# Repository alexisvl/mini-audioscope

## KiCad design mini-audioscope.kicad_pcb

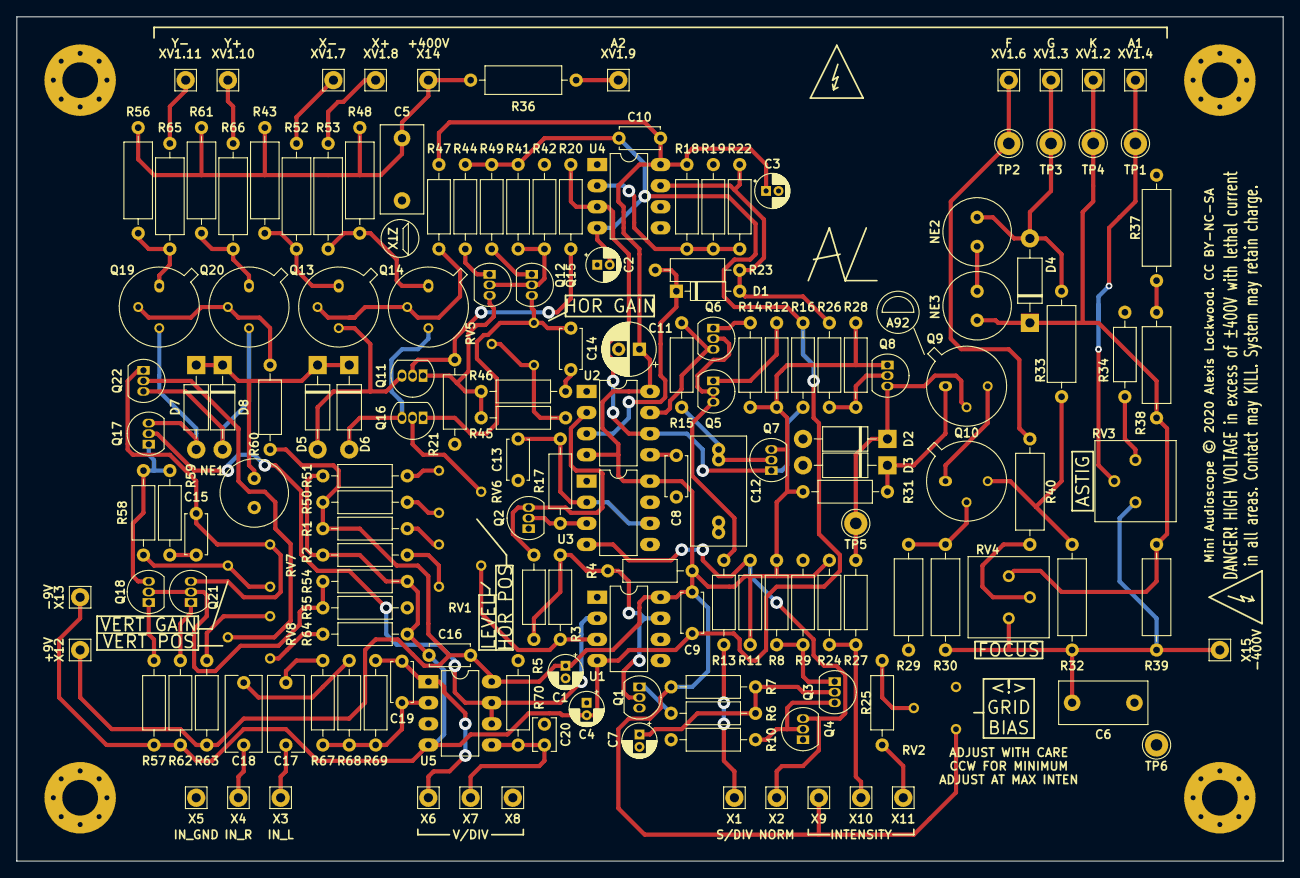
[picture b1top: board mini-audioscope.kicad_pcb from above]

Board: 2 copper layers, 152.4 x 101.6 mm, 169 parts (0 on the bottom side), 90 nets.

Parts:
C1, C2, C3, C4: 33µ; CP_Radial_D4.0mm_P1.50mm
C5, C6: 22n; C_Disc_D10.5mm_W5.0mm_P7.50mm
C7: 3µ3; CP_Radial_D4.0mm_P1.50mm
C8: 10n; C_Disc_D4.7mm_W2.5mm_P5.00mm
C9, C10, C16: 100n; C_Disc_D4.7mm_W2.5mm_P5.00mm
C11: 47µ; CP_Radial_D6.3mm_P2.50mm
C12: 470n; C_Rect_L13.0mm_W6.5mm_P7.50mm_P10.00mm
C13: 470n; C_Disc_D4.7mm_W2.5mm_P5.00mm
C14, C15: DNP; C_Disc_D4.7mm_W2.5mm_P5.00mm
C17, C18: 220n; C_Rect_L9.0mm_W4.2mm_P7.50mm_MKT
C19: 47p; C_Disc_D4.7mm_W2.5mm_P5.00mm
C20: 22p; C_Disc_D3.8mm_W2.6mm_P2.50mm
D1: 1N4148; D_DO-35_SOD27_P7.62mm_Horizontal
D2, D3, D4, D5, D6, D7, D8: 1N4007; D_DO-41_SOD81_P10.16mm_Horizontal
H1, H2, H3, H4: GND; MountingHole_4.3mm_M4_Pad_Via
NE1, NE2, NE3: A9A; C_Radial_D8.0mm_H11.5mm_P3.50mm
Q1, Q3, Q5, Q6, Q8: 2N3906; TO-92_Inline
Q2: 2N7000; TO-92_Inline
Q4, Q7, Q12, Q15, Q18, Q21: 2N3904; TO-92_Inline
Q9, Q10: MPSA92; TO-5-3
Q11, Q16, Q17, Q22: 2N5551; TO-92_Inline
Q13, Q14, Q19, Q20: ZTX458; TO-5-3
R1, R2: 27k; R_Axial_DIN0207_L6.3mm_D2.5mm_P10.16mm_Horizontal
R3, R22: 4M7; R_Axial_DIN0207_L6.3mm_D2.5mm_P10.16mm_Horizontal
R4, R8, R11, R18, R19, R20, R23, R27, R41, R42, R47, R54, R55, R60: 10k; R_Axial_DIN0207_L6.3mm_D2.5mm_P10.16mm_Horizontal
R5, R7, R10, R67, R68, R69: 100k; R_Axial_DIN0207_L6.3mm_D2.5mm_P10.16mm_Horizontal
R6: 10; R_Axial_DIN0207_L6.3mm_D2.5mm_P10.16mm_Horizontal
R9: 22k; R_Axial_DIN0207_L6.3mm_D2.5mm_P10.16mm_Horizontal
R12, R13, R14: 470; R_Axial_DIN0207_L6.3mm_D2.5mm_P10.16mm_Horizontal
R15: 100; R_Axial_DIN0207_L6.3mm_D2.5mm_P10.16mm_Horizontal
R16: 6k8; R_Axial_DIN0207_L6.3mm_D2.5mm_P10.16mm_Horizontal
R17: 75k; R_Axial_DIN0207_L6.3mm_D2.5mm_P10.16mm_Horizontal
R21: 2k7; R_Axial_DIN0207_L6.3mm_D2.5mm_P10.16mm_Horizontal
R24: 470k; R_Axial_DIN0207_L6.3mm_D2.5mm_P10.16mm_Horizontal
R25: 1k; R_Axial_DIN0207_L6.3mm_D2.5mm_P10.16mm_Horizontal
R26: 33k; R_Axial_DIN0207_L6.3mm_D2.5mm_P10.16mm_Horizontal
R28, R34: 180k; R_Axial_DIN0207_L6.3mm_D2.5mm_P10.16mm_Horizontal
R29, R30, R32, R39, R43, R48, R56, R61: 220k/HW; R_Axial_DIN0309_L9.0mm_D3.2mm_P12.70mm_Horizontal
R31: 20k; R_Axial_DIN0207_L6.3mm_D2.5mm_P10.16mm_Horizontal
R33, R40: 100k/HW; R_Axial_DIN0309_L9.0mm_D3.2mm_P12.70mm_Horizontal
R36, R52, R53, R65, R66: 10k/HW; R_Axial_DIN0309_L9.0mm_D3.2mm_P12.70mm_Horizontal
R37, R38: 390k/HW; R_Axial_DIN0309_L9.0mm_D3.2mm_P12.70mm_Horizontal
R44, R49, R50, R51, R57, R62, R63, R64: 8k2; R_Axial_DIN0207_L6.3mm_D2.5mm_P10.16mm_Horizontal
R45, R58: 1k5; R_Axial_DIN0207_L6.3mm_D2.5mm_P10.16mm_Horizontal
R46, R59: DNP; R_Axial_DIN0207_L6.3mm_D2.5mm_P10.16mm_Horizontal
R70: 1M; R_Axial_DIN0207_L6.3mm_D2.5mm_P10.16mm_Horizontal
RV1, RV2, RV5, RV7: 5k; stock_pot
RV3: 500k; Potentiometer_Bourns_3386P_Vertical
RV4: 1M; Potentiometer_Bourns_3386P_Vertical
RV6, RV8: 2k; stock_pot
TP1: V(A1); TestPoint_Loop_D2.60mm_Drill1.4mm_Beaded
TP2: V(F); TestPoint_Loop_D2.60mm_Drill1.4mm_Beaded
TP3: V(G); TestPoint_Loop_D2.60mm_Drill1.4mm_Beaded
TP4: V(K); TestPoint_Loop_D2.60mm_Drill1.4mm_Beaded
TP5: INTEN; TestPoint_Loop_D2.60mm_Drill1.4mm_Beaded
TP6: GND; TestPoint_Loop_D2.60mm_Drill1.4mm_Beaded
U1, U4: LM311; DIP-8_W7.62mm_LongPads
U2, U3: NE555P; DIP-8_W7.62mm_LongPads
U5: TL072; DIP-8_W7.62mm_LongPads
X1: S/DIV; Pin_D1.1mm_L8.5mm_W2.5mm_FlatFork
X2: NORM; Pin_D1.1mm_L8.5mm_W2.5mm_FlatFork
X3: L; Pin_D1.1mm_L8.5mm_W2.5mm_FlatFork
X4: R; Pin_D1.1mm_L8.5mm_W2.5mm_FlatFork
X5: G; Pin_D1.1mm_L8.5mm_W2.5mm_FlatFork
X6: G+; Pin_D1.1mm_L8.5mm_W2.5mm_FlatFork
X7: GW; Pin_D1.1mm_L8.5mm_W2.5mm_FlatFork
X8: G-; Pin_D1.1mm_L8.5mm_W2.5mm_FlatFork
X9: I+; Pin_D1.1mm_L8.5mm_W2.5mm_FlatFork
X10: IW; Pin_D1.1mm_L8.5mm_W2.5mm_FlatFork
X11: I-; Pin_D1.1mm_L8.5mm_W2.5mm_FlatFork
X12: +9; Pin_D1.1mm_L8.5mm_W2.5mm_FlatFork
X13: -9; Pin_D1.1mm_L8.5mm_W2.5mm_FlatFork
X14: +400; Pin_D1.1mm_L8.5mm_W2.5mm_FlatFork
X15: -400; Pin_D1.1mm_L8.5mm_W2.5mm_FlatFork
XV1.2: K; Pin_D1.1mm_L8.5mm_W2.5mm_FlatFork
XV1.3: G; Pin_D1.1mm_L8.5mm_W2.5mm_FlatFork
XV1.4: A1; Pin_D1.1mm_L8.5mm_W2.5mm_FlatFork
XV1.6: F; Pin_D1.1mm_L8.5mm_W2.5mm_FlatFork
XV1.7: X-; Pin_D1.1mm_L8.5mm_W2.5mm_FlatFork
XV1.8: X+; Pin_D1.1mm_L8.5mm_W2.5mm_FlatFork
XV1.9: A2; Pin_D1.1mm_L8.5mm_W2.5mm_FlatFork
XV1.10: V+; Pin_D1.1mm_L8.5mm_W2.5mm_FlatFork
XV1.11: V-; Pin_D1.1mm_L8.5mm_W2.5mm_FlatFork

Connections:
+9V: C1.1, C3.1, C9.1, C10.1, C11.1, C16.2, Q7.3, Q8.1, R1.2, R4.1, R7.1, R8.1, R11.1, R12.1, R14.1, R18.1, R24.1, R28.1, R31.1, R47.1, R50.2, R60.1, R63.2, RV2.1, U1.8, U2.4, U2.8, U3.8, U4.8, U5.8, X9.1, X12.1
+400V: C5.1, R36.1, R43.1, R48.1, R56.1, R61.1, X14.1
-9V: C2.2, C4.2, C9.2, C10.2, C16.1, R2.1, R16.2, R41.1, R44.2, R49.2, R51.1, R54.1, R57.2, R62.2, R64.1, U1.4, U4.4, U5.4, X13.1
-400V: C6.1, R30.1, R32.1, R39.2, RV3.3, RV4.1, X15.1
/A1: RV3.2, TP1.1, XV1.4.1
/A2: R36.2, XV1.9.1
/CLAMP: D5.1, D6.1, D7.1, D8.1, NE1.2
/CRT Bias/NC250_1: R37.2, R38.1
/CRT Bias/NC250_2: Q9.3, Q10.1
/CRT Bias/NC250_3: Q10.2, R29.2, R30.2
/CRT Bias/NC250_4: R40.1, RV4.2
/CRT Bias/NC250_5: NE2.2, NE3.1
/CRT Bias/NC400_3: Q10.3, R32.2, R33.1
/DEFLX+: R53.2, XV1.8.1
/DEFLX-: R52.2, XV1.7.1
/DEFLY+: R66.2, XV1.10.1
/DEFLY-: R65.2, XV1.11.1
/F: R40.2, TP2.1, XV1.6.1
/G: D4.2, NE2.1, R33.2, TP3.1, XV1.3.1
/GAIN_IN: C20.2, R70.2, U5.5, X7.1
/GAIN_OUT: C19.2, R69.2, U5.1, X6.1
/Horiz Defl/DEFL_INT+: Q14.1, R48.2, R53.1
/Horiz Defl/DEFL_INT-: Q13.1, R43.2, R52.1
/INTEN_B: R25.1, X11.1
/INTEN_W: R24.2, R27.1, X10.1
/K: D4.1, NE3.2, R38.2, R39.1, RV4.3, TP4.1, XV1.2.1
/L: C17.1, X3.1
/OUT: Q17.2, U1.2, U5.6, U5.7
/R: C18.1, X4.1
/SLOPE: R13.2, X1.1
/Sweep/AUTO_TRIGGER: Q2.2, R17.1, U3.3
/Sweep/SWEEP_EN: D1.1, R23.1, U2.3
/Sweep/~TRIG: Q2.3, R5.2, U2.2
/Vert Defl/DEFL_INT+: Q20.1, R61.2, R66.1
/Vert Defl/DEFL_INT-: Q19.1, R56.2, R65.1
/X: Q11.2, R20.2, R21.1
/~BLANK: D1.2, R22.2, R23.2, R26.1, U4.7
/~NORM: Q4.3, R11.2, U3.4, X2.1
GND: C1.2, C2.1, C3.2, C4.1, C5.2, C6.2, C7.2, C8.1, C11.2, C12.2, C13.2, C20.1, D2.2, D3.2, H1.1, H2.1, H3.1, H4.1, NE1.1, Q1.3, Q2.1, Q4.1, R9.2, R10.2, R19.2, R21.2, R29.1, R34.1, R37.1, R42.2, R55.2, R70.1, RV2.3, TP6.1, U1.1, U2.1, U3.1, U4.1, U5.3, X5.1, X8.1
unnamed: C7.1, Q3.2, R6.1, R7.2
unnamed: C8.2, U2.5
unnamed: C12.1, Q7.2, R15.1
unnamed: C13.1, R17.2, U3.2, U3.6
unnamed: C14.1, R46.2
unnamed: C14.2, Q15.3, Q16.1, RV5.3
unnamed: C15.1, R59.2
unnamed: C15.2, Q21.3, Q22.1, RV7.3
unnamed: C17.2, R67.1
unnamed: C18.2, R68.1
unnamed: C19.1, R67.2, R68.2, R69.1, U5.2
unnamed: D2.1, Q8.3, Q9.2, R27.2, TP5.1
unnamed: D3.1, Q9.1, R31.2
unnamed: D5.2, Q11.3, Q13.3
unnamed: D6.2, Q14.3, Q16.3
unnamed: D7.2, Q17.3, Q19.3
unnamed: D8.2, Q20.3, Q22.3
unnamed: Q1.1, R6.2
unnamed: Q1.2, R3.2, R4.2, R5.1, U1.7
unnamed: Q3.1, R8.2, R9.1
unnamed: Q3.3, Q4.2, R10.1
unnamed: Q5.1, R12.2
unnamed: Q5.2, Q5.3, Q6.2, R13.1
unnamed: Q6.1, R14.2
unnamed: Q6.3, R15.2, U2.7
unnamed: Q7.1, R16.1, R20.1, U2.6, U4.3
unnamed: Q8.2, R26.2, R28.2
unnamed: Q11.1, Q12.3, R45.1, R46.1
unnamed: Q12.1, R44.1
unnamed: Q12.2, Q15.2, R41.2, R42.1
unnamed: Q13.2, Q14.2, R47.2
unnamed: Q15.1, R49.1
unnamed: Q16.2, RV6.2
unnamed: Q17.1, Q18.3, R58.1, R59.1
unnamed: Q18.1, R57.1
unnamed: Q18.2, Q21.2, R54.2, R55.1
unnamed: Q19.2, Q20.2, R60.2
unnamed: Q21.1, R62.1
unnamed: Q22.2, RV8.2
unnamed: R1.1, RV1.1
unnamed: R2.2, RV1.3
unnamed: R3.1, RV1.2, U1.3
unnamed: R18.2, R19.1, R22.1, U4.2
unnamed: R25.2, RV2.2
unnamed: R34.2, RV3.1
unnamed: R45.2, RV5.1, RV5.2
unnamed: R50.1, RV6.3
unnamed: R51.2, RV6.1
unnamed: R58.2, RV7.1, RV7.2
unnamed: R63.1, RV8.3
unnamed: R64.2, RV8.1

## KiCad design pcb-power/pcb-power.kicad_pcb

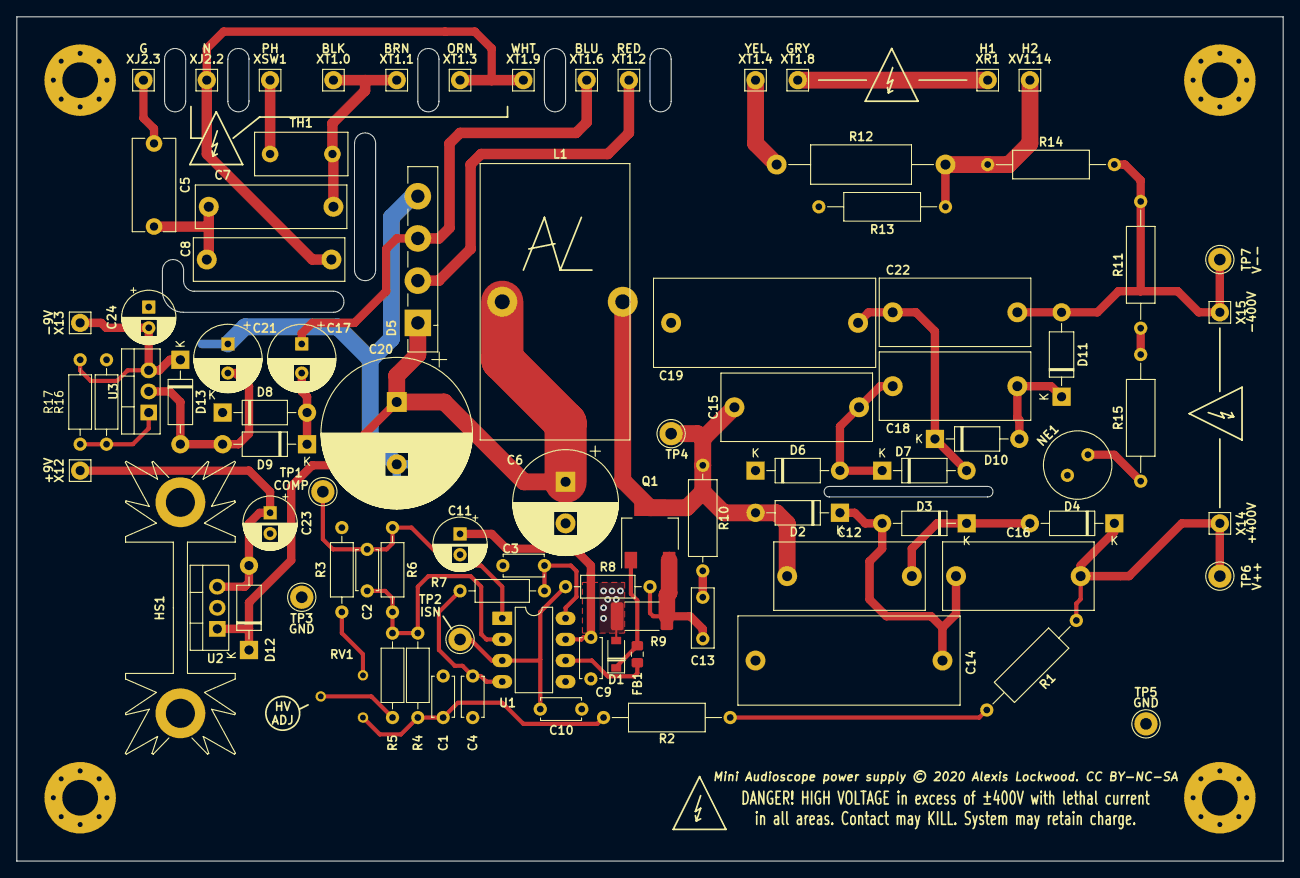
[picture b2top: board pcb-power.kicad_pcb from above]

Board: 2 copper layers, 152.4 x 101.6 mm, 92 parts (0 on the bottom side), 40 nets.

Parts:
C1, C10: 100p; C_Disc_D4.7mm_W2.5mm_P5.00mm
C2: 470p; C_Disc_D4.7mm_W2.5mm_P5.00mm
C3, C9: 100n; C_Disc_D4.7mm_W2.5mm_P5.00mm
C4: 4n7; C_Disc_D4.7mm_W2.5mm_P5.00mm
C5: 2n2/Y2; C_Disc_D11.0mm_W5.0mm_P10.00mm
C6: 470u; CP_Radial_D12.5mm_P5.00mm
C7, C8: 47n/X2; C_Rect_L18.0mm_W5.0mm_P15.00mm_FKS3_FKP3
C11, C23, C24: 47u; CP_Radial_D6.3mm_P2.50mm
C12, C15, C16, C18, C22: 1u/450; C_Rect_L18.0mm_W8.0mm_P15.00mm_FKS3_FKP3
C13: 100p/500V; C_Disc_D7.0mm_W2.5mm_P5.00mm
C14, C19: 3u3/450; C_Rect_L26.5mm_W10.5mm_P22.50mm_MKS4
C17, C21: 220u; CP_Radial_D8.0mm_P3.50mm
C20: 3300u; CP_Radial_D18.0mm_P7.50mm
D1: MBR0540; D_SOD-123
D2, D3, D4, D6, D7, D10, D11: UF4007; D_DO-41_SOD81_P10.16mm_Horizontal
D5: GBU4J; Diode_Bridge_Vishay_GBU
D8, D9: 1N4007; D_DO-41_SOD81_P10.16mm_Horizontal
D12, D13: 1N4004; D_DO-41_SOD81_P10.16mm_Horizontal
FB1: 742792023; L_0805_2012Metric_Pad1.15x1.40mm_HandSolder
H1, H2, H3, H4: GND; MountingHole_4.3mm_M4_Pad_Via
HS1: 513102B02500G; Heatsink_Fischer_SK104-STCB_35x13mm__2xDrill3.5mm_ScrewM3
L1: 150u/5A; L_Toroid_Vertical_L33.0mm_W17.8mm_P12.70mm_Pulse_KM-5
NE1: A9A; C_Radial_D8.0mm_H11.5mm_P3.50mm
Q1: IPN70R1K5CE; SOT-223-3_TabPin2
R1, R2: 330k/½W; R_Axial_DIN0309_L9.0mm_D3.2mm_P15.24mm_Horizontal
R3: 3k9; R_Axial_DIN0207_L6.3mm_D2.5mm_P10.16mm_Horizontal
R4: 10k; R_Axial_DIN0207_L6.3mm_D2.5mm_P10.16mm_Horizontal
R5, R7: 3k3; R_Axial_DIN0207_L6.3mm_D2.5mm_P10.16mm_Horizontal
R6: 150k; R_Axial_DIN0207_L6.3mm_D2.5mm_P10.16mm_Horizontal
R8: 1k; R_Axial_DIN0207_L6.3mm_D2.5mm_P10.16mm_Horizontal
R9: 0R27/1W; R_2512_6332Metric_Pad1.52x3.35mm_HandSolder
R10: 1k5/½W; R_Axial_DIN0309_L9.0mm_D3.2mm_P12.70mm_Horizontal
R11: 270k/HW; R_Axial_DIN0309_L9.0mm_D3.2mm_P15.24mm_Horizontal
R12: 3R9/1W; R_Axial_DIN0414_L11.9mm_D4.5mm_P20.32mm_Horizontal
R13: 680k/HW; R_Axial_DIN0309_L9.0mm_D3.2mm_P15.24mm_Horizontal
R14, R15: 220k/HW; R_Axial_DIN0309_L9.0mm_D3.2mm_P15.24mm_Horizontal
R16: 750; R_Axial_DIN0207_L6.3mm_D2.5mm_P10.16mm_Horizontal
R17: 120; R_Axial_DIN0207_L6.3mm_D2.5mm_P10.16mm_Horizontal
RV1: 500; stock_pot
TH1: 60/800mA; C_Disc_D11.0mm_W5.0mm_P7.50mm
TP1: COMP; TestPoint_Loop_D2.60mm_Drill1.4mm_Beaded
TP2: ISN; TestPoint_Loop_D2.60mm_Drill1.4mm_Beaded
TP3, TP5: GND; TestPoint_Loop_D2.60mm_Drill1.4mm_Beaded
TP4: VSW; TestPoint_Loop_D2.60mm_Drill1.4mm_Beaded
TP6: V++; TestPoint_Loop_D2.60mm_Drill1.4mm_Beaded
TP7: V--; TestPoint_Loop_D2.60mm_Drill1.4mm_Beaded
U1: UC3843; DIP-8_W7.62mm_LongPads
U2: 7809; TO-220-3_Vertical
U3: LM337; TO-220-3_Vertical
X12: +9V; Pin_D1.1mm_L8.5mm_W2.5mm_FlatFork
X13: -9V; Pin_D1.1mm_L8.5mm_W2.5mm_FlatFork
X14: +400V; Pin_D1.1mm_L8.5mm_W2.5mm_FlatFork
X15: -400V; Pin_D1.1mm_L8.5mm_W2.5mm_FlatFork
XJ2.2: N; Pin_D1.1mm_L8.5mm_W2.5mm_FlatFork
XJ2.3: G; Pin_D1.1mm_L8.5mm_W2.5mm_FlatFork
XR1: H1; Pin_D1.1mm_L8.5mm_W2.5mm_FlatFork
XSW1: PH; Pin_D1.1mm_L8.5mm_W2.5mm_FlatFork
XT1.0: BLK; Pin_D1.1mm_L8.5mm_W2.5mm_FlatFork
XT1.1: BRN; Pin_D1.1mm_L8.5mm_W2.5mm_FlatFork
XT1.2: RED; Pin_D1.1mm_L8.5mm_W2.5mm_FlatFork
XT1.3: ORN; Pin_D1.1mm_L8.5mm_W2.5mm_FlatFork
XT1.4: YEL; Pin_D1.1mm_L8.5mm_W2.5mm_FlatFork
XT1.6: BLU; Pin_D1.1mm_L8.5mm_W2.5mm_FlatFork
XT1.8: GRY; Pin_D1.1mm_L8.5mm_W2.5mm_FlatFork
XT1.9: WHT; Pin_D1.1mm_L8.5mm_W2.5mm_FlatFork
XV1.14: H2; Pin_D1.1mm_L8.5mm_W2.5mm_FlatFork

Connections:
+9V: C9.1, C11.1, U1.7
+15UNREG: C6.1, C20.1, D5.1, D12.1, L1.1, U2.1
/+400V: C16.2, D4.1, R1.1, TP6.1, X14.1
/-400V: C22.2, D11.2, R11.2, R14.2, TP7.1, X15.1
/H1: XR1.1, XT1.8.1
/H2: R12.1, XT1.4.1
/H2_2: R12.2, R13.1, R14.1, XV1.14.1
/HALFFB_250: R1.2, R2.2
/LINE: TH1.1, XSW1.1
/LINE_NTC: C7.1, TH1.2, XT1.0.1, XT1.1.1
/MULT1_400: C12.2, D3.1, D4.2
/MULT2_250: C14.2, C16.1, D2.1, D3.2
/MULT3_400: C18.2, D10.2, D11.1
/MULT4_250: C19.2, C22.1, D7.2, D10.1
/MULT5_250: C15.2, C18.1, D6.2, D7.1
/NEON_250: R11.1, R15.2
/NEUT: C8.2, XJ2.2.1, XT1.3.1, XT1.9.1
/SNUB: C13.2, R10.2
/VSW: C12.1, C15.1, D2.2, L1.2, Q1.2, R10.1, TP4.1
/X2_CENT: C5.2, C7.2, C8.1
GND: C1.2, C3.2, C4.2, C5.1, C6.2, C9.2, C10.2, C11.2, C14.1, C19.1, C20.2, C21.1, C23.2, C24.1, D1.2, D5.4, D6.1, D8.1, H1.1, H2.1, H3.1, H4.1, HS1.1, NE1.2, R3.1, R9.2, R13.2, R16.1, TP3.1, TP5.1, U1.5, U2.2, XJ2.3.1
unnamed: C1.1, R2.1, R4.2, RV1.1
unnamed: C2.1, R4.1, R5.1, R6.2, U1.2
unnamed: C2.2, R6.1, TP1.1, U1.1
unnamed: C3.1, R7.1, U1.8
unnamed: C4.1, R7.2, U1.4
unnamed: C10.1, R8.1, TP2.1, U1.3
unnamed: C13.1, Q1.3, R8.2, R9.1
unnamed: C17.1, D5.3, XT1.6.1
unnamed: C17.2, D8.2, D9.1
unnamed: C21.2, D9.2, D13.2, U3.2
unnamed: C23.1, D12.2, U2.3, X12.1
unnamed: C24.2, D13.1, R17.1, U3.3, X13.1
unnamed: D1.1, FB1.2, Q1.1
unnamed: D5.2, XT1.2.1
unnamed: FB1.1, U1.6
unnamed: NE1.1, R15.1
unnamed: R3.2, RV1.3
unnamed: R5.2, RV1.2
unnamed: R16.2, R17.2, U3.1

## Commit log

2020-03-04 Commit what I have...
2020-03-04 Add datasheets
2020-03-05 Power supply changes
2020-03-05 Better auto sweep timeout circuit
2020-03-05 Bring back the norm switch
2020-03-08 Commit before re-routing
2020-03-08 Before second re-route
2020-03-11 savesavesave
2020-03-11 Cleaned up
2020-03-20 Version sent to fab
2020-03-29 Schematic updates

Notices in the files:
mini-audioscope.kicad_pcb:
Mini Audioscope © 2020 Alexis Lockwood. CC BY-NC-SA
pcb-power/pcb-power.kicad_pcb:
Mini Audioscope power supply © 2020 Alexis Lockwood. CC BY-NC-SA
